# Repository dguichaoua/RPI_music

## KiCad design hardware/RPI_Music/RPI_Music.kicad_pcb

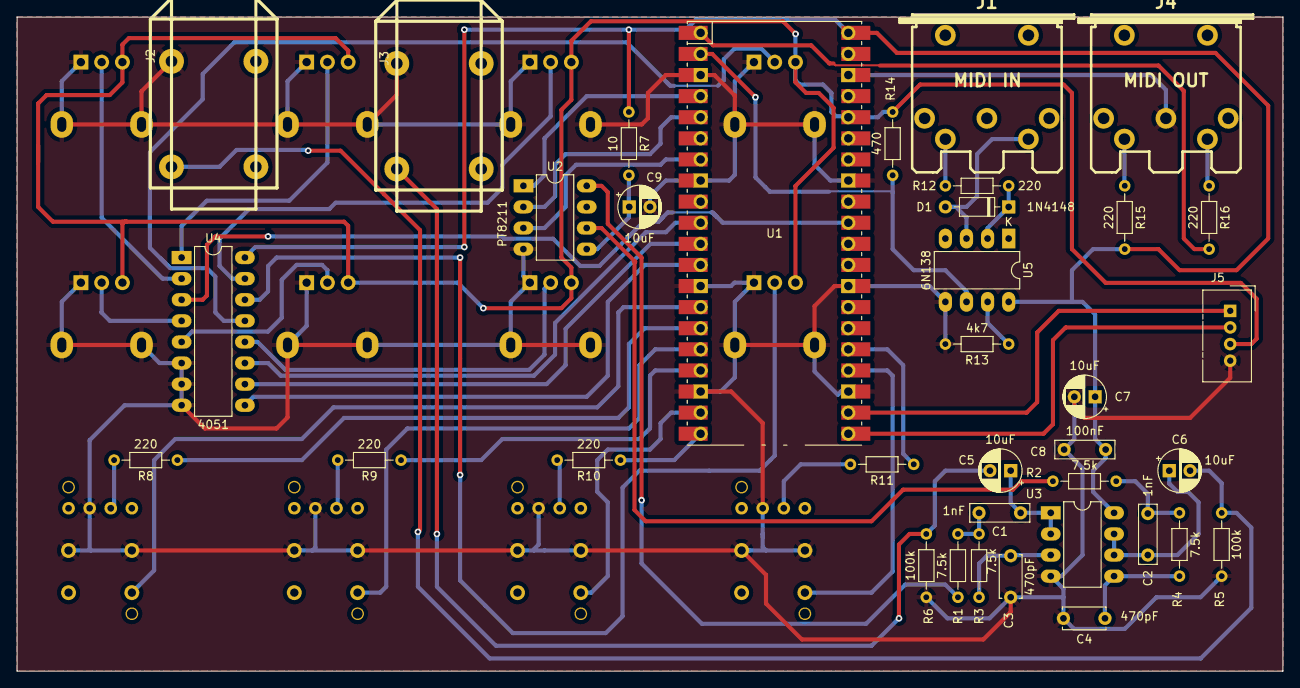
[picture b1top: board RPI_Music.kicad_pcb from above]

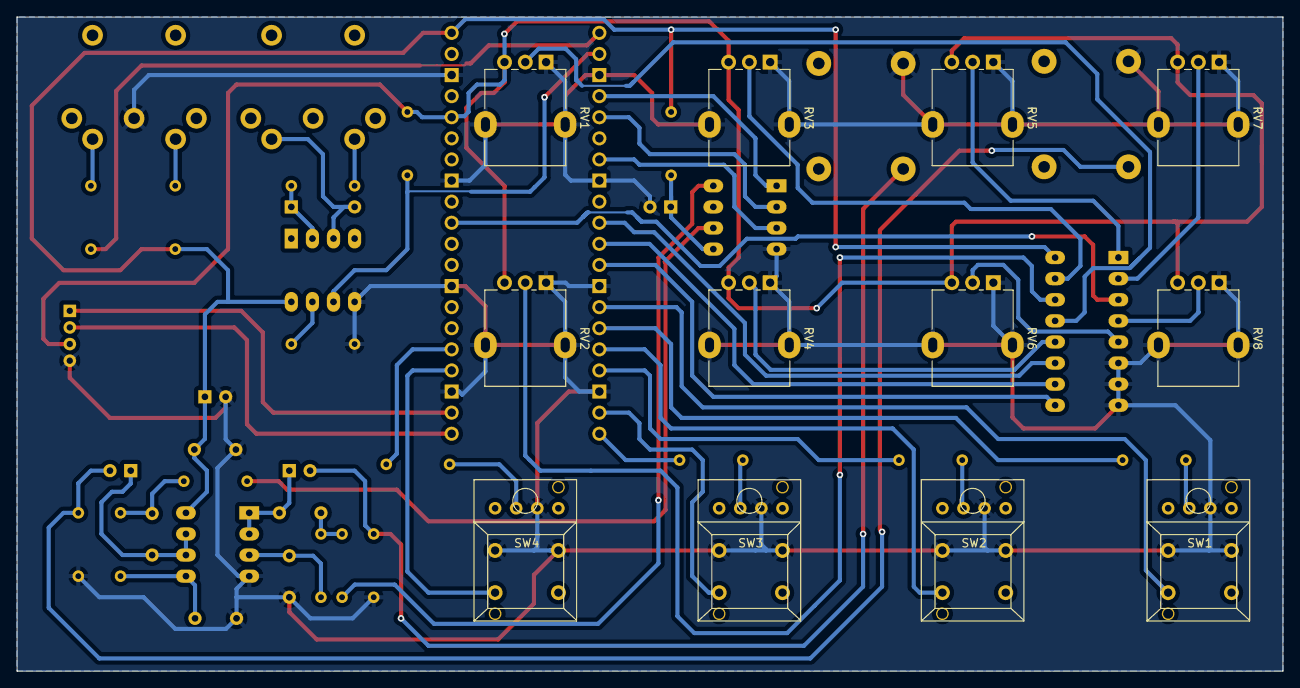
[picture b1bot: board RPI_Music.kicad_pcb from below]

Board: 2 copper layers, 152.4 x 78.7 mm, 48 parts (12 on the bottom side), 51 nets.

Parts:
C1, C2: 1nF; C_Rect_L7.0mm_W2.0mm_P5.00mm
C3, C4: 470pF; C_Disc_D5.0mm_W2.5mm_P5.00mm
C5, C6, C7, C9: 10uF; CP_Radial_D5.0mm_P2.50mm
C8: 100nF; C_Rect_L7.0mm_W2.0mm_P5.00mm
D1: 1N4148; D_DO-35_SOD27_P7.62mm_Horizontal
J1: MIDI IN; MIDI_DIN5
J2, J3: AudioJack2; AudioJackMono
J4: MIDI OUT; MIDI_DIN5
J5: I2C; NS-Tech_Grove_1x04_P2mm_Vertical
R1, R2, R3, R4: 7.5k; R_Axial_DIN0204_L3.6mm_D1.6mm_P7.62mm_Horizontal
R5, R6: 100k; R_Axial_DIN0204_L3.6mm_D1.6mm_P7.62mm_Horizontal
R7: 10; R_Axial_DIN0204_L3.6mm_D1.6mm_P7.62mm_Horizontal
R8, R9, R10, R11, R12, R15, R16: 220; R_Axial_DIN0204_L3.6mm_D1.6mm_P7.62mm_Horizontal
R13: 4k7; R_Axial_DIN0204_L3.6mm_D1.6mm_P7.62mm_Horizontal
R14: 470; R_Axial_DIN0204_L3.6mm_D1.6mm_P7.62mm_Horizontal
RV1, RV2, RV3, RV4, RV5, RV6, RV7, RV8: 10k; Potentiometer_Alpha_RD901F-40-00D_Single_Vertical
SW1, SW2, SW3, SW4: S1; Push_LED
U1: Pico; RPi_Pico_SMD_TH
U2: PT8211; DIP-8_W7.62mm_LongPads
U3: MCP6002; DIP-8_W7.62mm_LongPads
U4: 4051; DIP-16_W7.62mm_LongPads
U5: 6N138; DIP-8_W7.62mm_LongPads

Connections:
+3.3V: J5.3, R14.1, RV1.3, RV2.3, RV3.3, RV4.3, RV5.3, RV6.3, RV7.3, RV8.3, U1.36 (3V3)
/ADC0: U1.31 (GPIO26_ADC0), U4.3 (X)
/BCK: U1.4 (GPIO2), U2.1
/DIN: U1.7 (GPIO5), U2.3
/GPIO7: U1.10 (GPIO7), U4.11 (A)
/GPIO8: U1.11 (GPIO8), U4.10 (B)
/GPIO9: U1.12 (GPIO9), U4.9 (C)
/GPIO10: SW1.2, U1.14 (GPIO10)
/GPIO11: R8.1, U1.15 (GPIO11)
/GPIO12: SW2.2, U1.16 (GPIO12)
/GPIO13: R9.1, U1.17 (GPIO13)
/GPIO14: SW3.2, U1.19 (GPIO14)
/GPIO15: R10.1, U1.20 (GPIO15)
/GPIO18: SW4.2, U1.24 (GPIO18)
/GPIO19: R11.1, U1.25 (GPIO19)
/LCH: R2.2, U2.6
/RCH: R1.2, U2.8
/Rx: R14.2, U1.2 (GPIO1), U5.6 (VO2)
/SCL: J5.1, U1.22 (GPIO17)
/SDA: J5.2, U1.21 (GPIO16)
/Tx: R16.2, U1.1 (GPIO0)
/WS: U1.5 (GPIO3), U2.2
GND: C3.2, C4.2, C7.2, C8.2, C9.2, J2.S, J3.S, J4.2, J5.4, R5.2, R6.2, R13.2, RV1.1, RV2.1, RV3.1, RV4.1, RV5.1, RV6.1, RV7.1, RV8.1, SW1.1, SW1.3 (K), SW2.1, SW2.3 (K), SW3.1, SW3.3 (K), SW4.1, SW4.3 (K), U1.3 (GND), U1.8 (GND), U1.13 (GND), U1.18 (GND), U1.23 (GND), U1.28 (GND), U1.33 (AGND), U1.38 (GND), U2.4, U3.4 (V-), U4.6 (~E), U4.7 (VEE), U4.8 (Vss), U5.5 (GND)
unnamed: C1.2, R1.1, R3.2
unnamed: C2.2, R2.1, R4.2
unnamed: C5.2, J3.T, R6.1
unnamed: C6.2, J2.T, R5.1
unnamed: D1.2 (A), J1.5, U5.3 (C2)
unnamed: D1.1 (K), R12.2, U5.2 (C1)
unnamed: J1.4, R12.1
unnamed: J4.4, R15.1
unnamed: J4.5, R16.1
unnamed: R8.2, SW1.4 (A)
unnamed: R9.2, SW2.4 (A)
unnamed: R10.2, SW3.4 (A)
unnamed: R11.2, SW4.4 (A)
unnamed: C9.1, R7.2, U2.5
unnamed: C3.1, R3.1, U3.3 (+)
unnamed: C1.1, C5.1, U3.1, U3.2 (-)
unnamed: C4.1, R4.1, U3.5 (+)
unnamed: C2.1, C6.1, U3.6 (-), U3.7
unnamed: RV1.2, U4.13 (X0)
unnamed: RV2.2, U4.14 (X1)
unnamed: RV3.2, U4.15 (X2)
unnamed: RV4.2, U4.12 (X3)
unnamed: RV5.2, U4.1 (X4)
unnamed: RV6.2, U4.5 (X5)
unnamed: RV7.2, U4.2 (X6)
unnamed: RV8.2, U4.4 (X7)
unnamed: R13.1, U5.7 (VO1)
VCC: C7.1, C8.1, R7.1, R15.2, U1.40 (VBUS), U3.8 (V+), U4.16 (Vdd), U5.8 (VCC)

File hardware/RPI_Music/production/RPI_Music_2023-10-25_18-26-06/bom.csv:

Designator,Footprint,Quantity,Value,LCSC Part #
"C1, C2",C_Rect_L7.0mm_W2.0mm_P5.00mm,2,1nF,
"C3, C4",C_Disc_D5.0mm_W2.5mm_P5.00mm,2,470pF,
"C5, C6, C7, C9",CP_Radial_D5.0mm_P2.50mm,4,10uF,
C8,C_Rect_L7.0mm_W2.0mm_P5.00mm,1,100nF,
D1,D_DO-35_SOD27_P7.62mm_Horizontal,1,1N4148,
J1,MIDI_DIN5,1,MIDI IN,
"J2, J3",AudioJackMono,2,AudioJack2,
J4,MIDI_DIN5,1,MIDI OUT,
J5,NS-Tech_Grove_1x04_P2mm_Vertical,1,I2C,
"R1, R2, R3, R4",R_Axial_DIN0204_L3.6mm_D1.6mm_P7.62mm_Horizontal,4,7.5k,
"R10, R11, R12, R15, R16, R8, R9",R_Axial_DIN0204_L3.6mm_D1.6mm_P7.62mm_Horizontal,7,220,
R13,R_Axial_DIN0204_L3.6mm_D1.6mm_P7.62mm_Horizontal,1,4k7,
R14,R_Axial_DIN0204_L3.6mm_D1.6mm_P7.62mm_Horizontal,1,470,
"R5, R6",R_Axial_DIN0204_L3.6mm_D1.6mm_P7.62mm_Horizontal,2,100k,
R7,R_Axial_DIN0204_L3.6mm_D1.6mm_P7.62mm_Horizontal,1,10,
"RV1, RV2, RV3, RV4, RV5, RV6, RV7, RV8",Potentiometer_Alpha_RD901F-40-00D_Single_Vertical,8,10k,
"SW1, SW2, SW3, SW4",Push_LED,4,S1,
U1,RPi_Pico_SMD_TH,1,Pico,
U2,DIP-8_W7.62mm_LongPads,1,PT8211,
U3,DIP-8_W7.62mm_LongPads,1,TL082,
U4,DIP-16_W7.62mm_LongPads,1,4051,
U5,DIP-8_W7.62mm_LongPads,1,6N138,

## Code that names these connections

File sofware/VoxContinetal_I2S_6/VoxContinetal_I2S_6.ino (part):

/*

    RPI PICO        PT8211
     GPIO2(4)     BCK (1)
     GPIO5(7)     DIN (3)
     GPIO3(5)       WS(2)
     GND            (4)
     +3.3V          (5)

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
